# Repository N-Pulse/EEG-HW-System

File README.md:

# EEG Hardware System

This repository contains the hardware design files for the N-Pulse EEG system.

The project is divided into three main subsystems:

- `eeg-board/` — EEG acquisition electronics
- `power-board/` — power supply, battery management, charging, and protection
- `headset/` — mechanical headset design and electrode integration

The electronic boards are designed in KiCad. Git is used for version control and collaboration between team members.

## Repository structure

```text
eeg-hw-system/
├── eeg-board/
├── power-board/
├── headset/
└── README.md

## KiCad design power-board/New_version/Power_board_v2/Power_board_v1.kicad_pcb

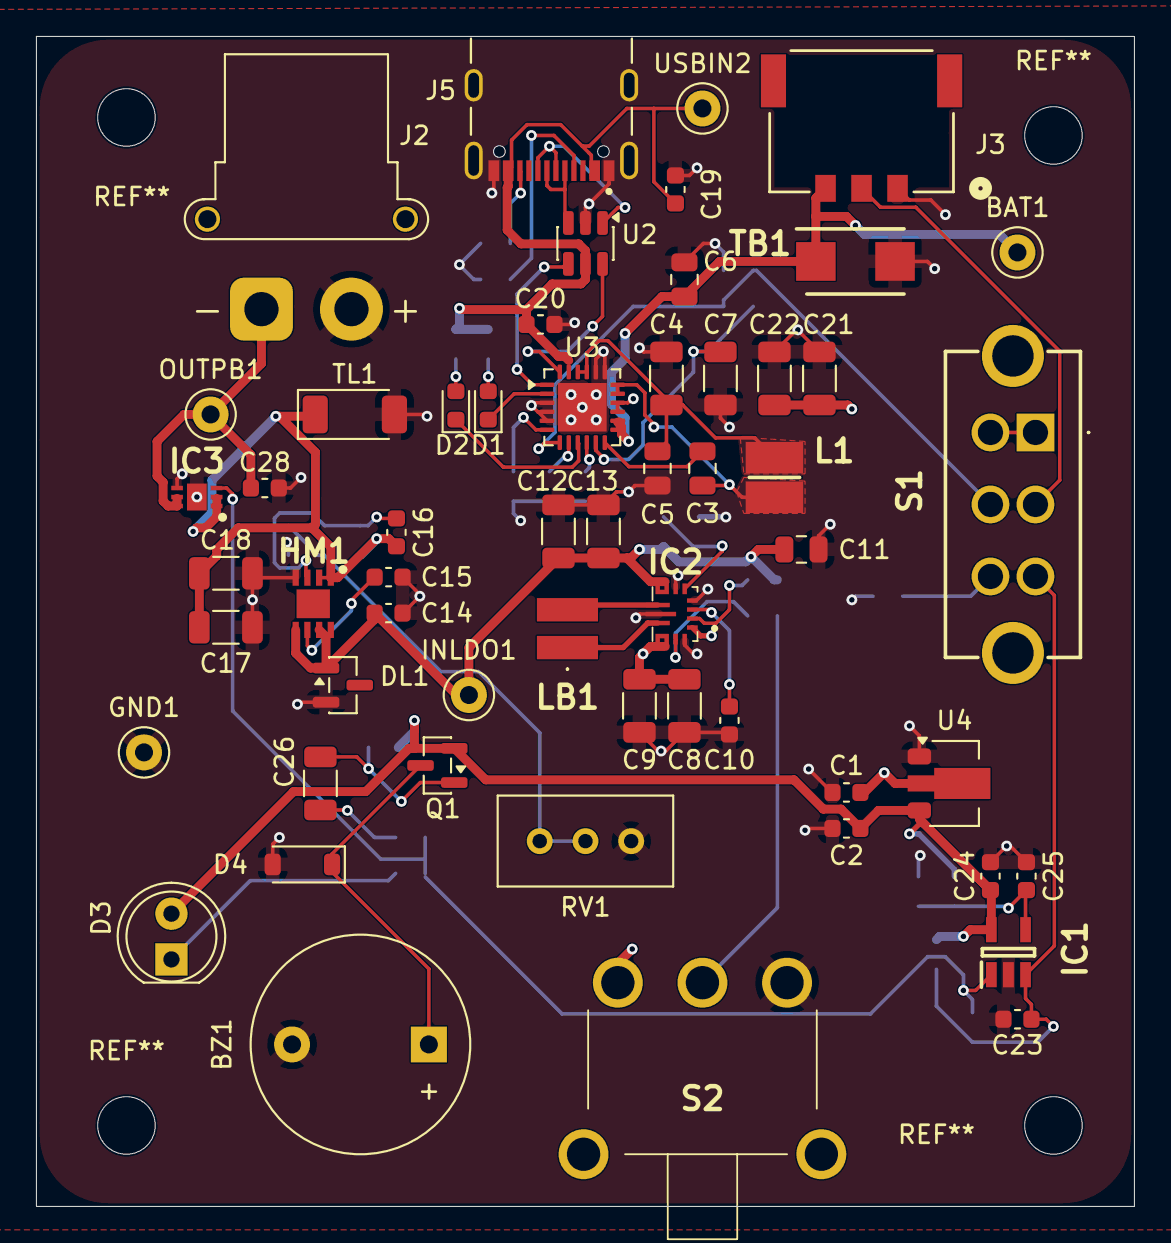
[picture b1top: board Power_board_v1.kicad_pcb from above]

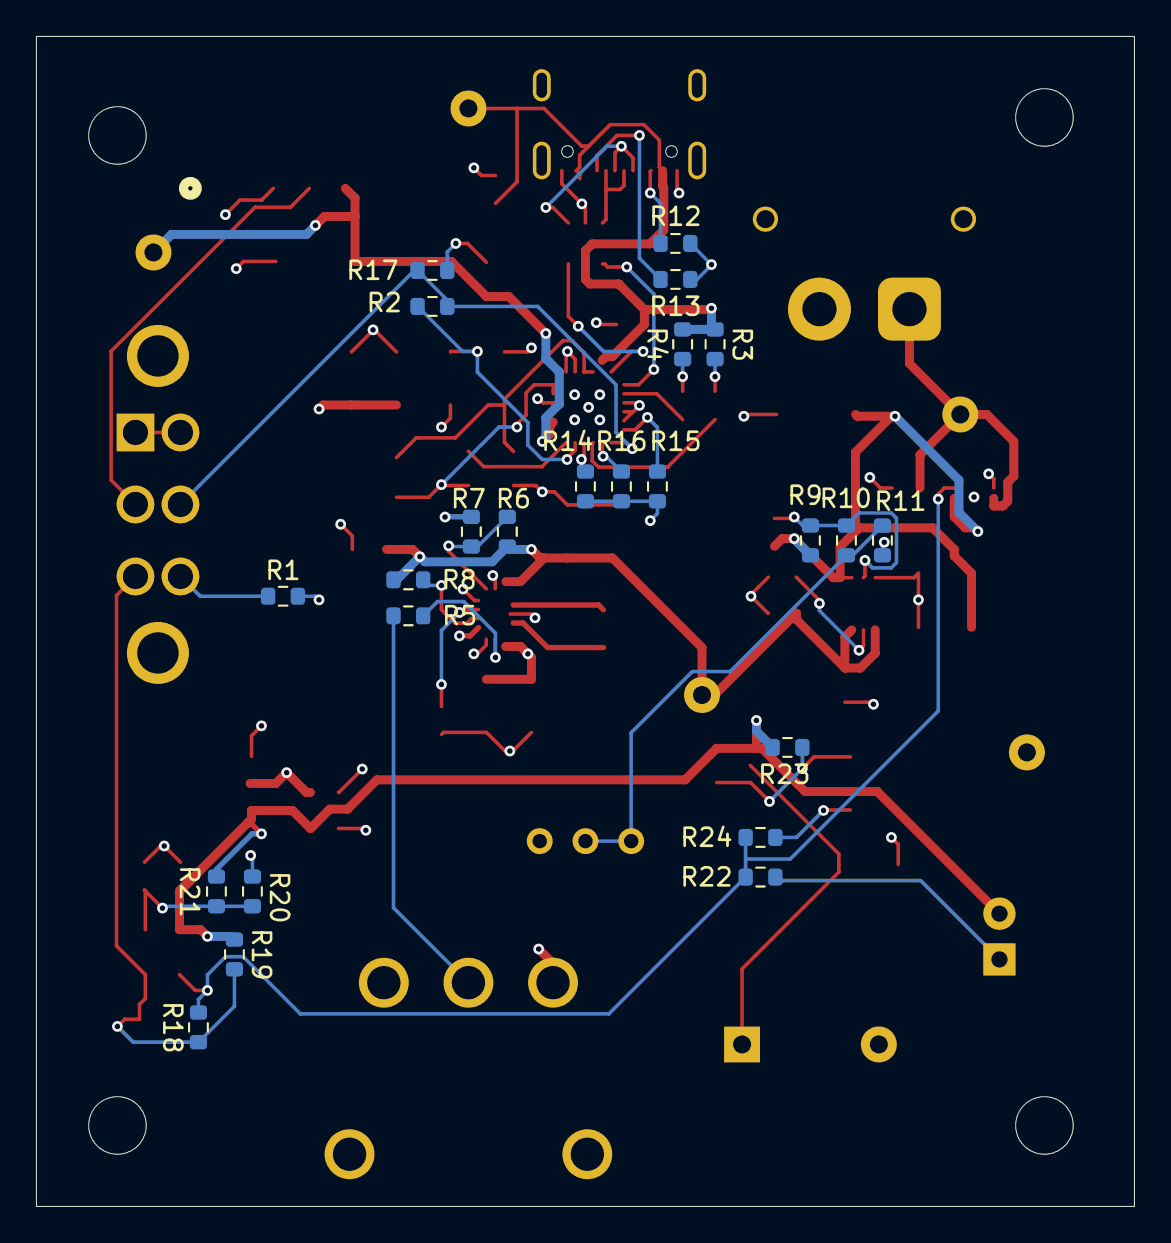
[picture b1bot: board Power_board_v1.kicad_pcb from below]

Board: 4 copper layers, 61.0 x 65.0 mm, 80 parts (24 on the bottom side), 46 nets.

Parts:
BAT1: TestPoint; TestPoint_Keystone_5000-5004_Miniature
BZ1: Buzzer; Buzzer_12x9.5RM7.6
C1, C2: 1uF; C_0603_1608Metric
C3: 47n; C_0805_2012Metric
C4, C21, C22: 22u; C_1206_3216Metric
C5, C6: 10u; C_0805_2012Metric
C7, C26: 4.7u; C_1206_3216Metric
C8, C9, C12, C13, C17, C18: 22uF; C_1206_3216Metric
C10, C14, C19, C23, C24, C25, C28: 100nF; C_0603_1608Metric
C11: 10uF; C_0805_2012Metric
C15: 220nF; C_0603_1608Metric
C16: 470nF; C_0603_1608Metric
C20: 1u; C_0603_1608Metric
D1, D2: LED_Small; LED_0603_1608Metric
D3: LED; LED_D5.0mm
D4: D; D_SOD-123
DL1: D_Zener; SOT-23
GND1: TestPoint; TestPoint_Keystone_5000-5004_Miniature
HM1: TPS7A8101DRBT; SON65P300X300X100-9N-D
IC1: MCP6541T-I_OT; SOT95P270X145-5N
IC2: TPS63070RNMR; TPS630701RNMR
IC3: AP2281-1FMG-7; SON50P201X181X60-7N
INLDO1: VinLDO; TestPoint_Keystone_5000-5004_Miniature
J2: XT30F; AMASS_XT30PW-F_1x02_P2.50mm_Horizontal
J3: 2053380003; CONN_2053380000-SD_03_MOL
J5: UJ20-C-H-G-SMT-1-P16-TR; SAMESKY_UJ20-C-H-G-SMT-1-P16-TR
L1: 1u; INDC3030X200N
LB1: 1.5uH; 78438336015
OUTPB1: VoutPB; TestPoint_Keystone_5000-5004_Miniature
Q1: BSS84; SOT-23
R1, R19, R20: 10k; R_0603_1608Metric
R2: 5.23k; R_0603_1608Metric
R3, R4, R24: 2.2k; R_0603_1608Metric
R5: 10kOhm; R_0603_1608Metric
R6: 665kOhm; R_0603_1608Metric
R7, R8: 100kOhm; R_0603_1608Metric
R9: 60.4k; R_0603_1608Metric
R10: 9.53k; R_0603_1608Metric
R11: 470; R_0603_1608Metric
R12, R13: 5.1k; R_0603_1608Metric
R14: 6.2k; R_0603_1608Metric
R15: 220k; R_0603_1608Metric
R16: 383; R_0603_1608Metric
R17: 30.1k; R_0603_1608Metric
R18: 51.1k; R_0603_1608Metric
R21: 26.7k; R_0603_1608Metric
R22: 330; R_0603_1608Metric
R23: 470k; R_0603_1608Metric
RV1: 0-500; Potentiometer_Bourns_3296W_Vertical
S1: MFS201N-9-Z; MFS201N9Z
S2: 5MS1S102AM6QES
TB1: D_Zener; DIOM5436X261N
TL1: D_SOD-128
U2: USBLC6-2SC6; SOT-23-6
U3: BQ25886RGE; Texas_RGE0024H_VQFN-24-1EP_4x4mm_P0.5mm_EP2.7x2.7mm
U4: MCP1703Ax-500xxMB; SOT-89-3
USBIN2: TestPoint; TestPoint_Keystone_5000-5004_Miniature

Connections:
/Buck 7.4 to 6.1V/EN: IC2.14 (EN), R5.2
/Buck 7.4 to 6.1V/FB: IC2.5 (FB), R6.2, R7.1
/Buck 7.4 to 6.1V/PG: IC2.2 (PG), R8.2
/Buck 7.4 to 6.1V/VAUX: C10.1, IC2.3 (VAUX)
/Buck 7.4 to 6.1V/VOUT BUCK BOOST: C11.1, C12.1, C13.1, C14.1, DL1.1 (K), HM1.5 (EN), HM1.7 (IN_1), HM1.8 (IN_2), IC2.7 (VOUT_1), IC2.8 (VOUT_2), IC2.17 (VOUT_1), INLDO1.1 (1_1), R6.1, R8.1
/Charging circuit/BTST: C3.2, U3.12 (BTST)
/Charging circuit/D+: U2.6 (I/O1), U3.24 (D+)
/Charging circuit/D-: U2.4 (I/O2), U3.1 (D-)
/Charging circuit/ICHGSET: R14.1, U3.10 (ICHGSET)
/Charging circuit/ILIM: R16.1, U3.8 (ILIM)
/Charging circuit/NTC: J3.2, S1.2 (COM_1)
/Charging circuit/PG: D2.1 (K), U3.9 (~PG)
/Charging circuit/PMID: C4.1, C5.1, L1.1, U3.21 (PMID), U3.22 (PMID)
/Charging circuit/REGN: C7.1, R2.1, U3.11 (REGN)
/Charging circuit/STAT: D1.1 (K), U3.2 (STAT)
/Charging circuit/SW: C3.1, L1.2, U3.17 (SW), U3.18 (SW)
/Charging circuit/SYS: C1.1, C8.1, C9.1, C21.1, C22.1, IC2.1 (PS/S), IC2.12 (VIN_1), IC2.13 (VIN_2), IC2.16 (VIN_1), S2.3 (NO), U3.15 (SYS), U3.16 (SYS), U4.2 (VI)
/Charging circuit/TS: R2.2, R17.1, S1.5 (COM_2), U3.7 (TS)
/Charging circuit/VBUS: C19.1, C20.1, J5.A4_B9 (VBUS), J5.B4_A9 (VBUS__1), R3.2, R4.2, U2.5 (VBUS), U3.23 (VBUS), USBIN2.1 (1_1)
/Charging circuit/VSET: R15.1, U3.6 (VSET)
/Temperature control/5V: C2.1, C24.1, D3.2 (A), IC1.5 (VDD), Q1.2 (S), R19.1, R21.1, R23.1, U4.3 (VO)
/Temperature control/INCOMP: C23.1, IC1.3 (VIN+), R18.1, R19.2, S1.3 (NC_1)
/Temperature control/OUT: IC1.1 (OUT), IC3.3 (EN), R18.2, R22.2, R24.2
BATTERY VOLTAGE: BAT1.1 (1_1), C6.1, J3.3, TB1.1 (K), U3.13 (BAT), U3.14 (BAT)
GND: BZ1.2 (-), C1.2, C2.2, C4.2, C5.2, C6.2, C7.2, C8.2, C9.2, C10.2, C11.2, C12.2, C13.2, C14.2, C15.2, C17.2, C18.2, C19.2, C20.2, C21.2, C22.2, C23.2, C24.2, C25.2, C28.2, D4.2 (A), DL1.2 (A), GND1.1 (1_1), HM1.4 (GND), IC1.2 (VSS), IC2.4 (GND), IC2.6 (FB2), IC2.10 (PGND), IC2.15 (VSEL), IC3.4 (GND_1), IC3.7 (GND_2), J2.2, J3.1, J5.A1_B12 (GND), J5.B1_A12 (GND__1), J5.SH1 (SHIELD), J5.SH2 (SHIELD__1), J5.SH3 (SHIELD__2), J5.SH4 (SHIELD__3), R1.2, R7.2, R11.2, R12.2, R13.2, R14.2, R15.2, R16.2, R17.2, R20.2, RV1.3, S2.1 (NC), TB1.2 (A), TL1.2 (A), U2.2 (GND), U3.3 (~CE), U3.4 (GND), U3.5 (OTG), U3.19 (GND), U3.20 (GND), U3.25 (GND), U4.1 (GND)
unnamed: BZ1.1 (+), D4.1 (K), Q1.3 (D)
unnamed: C26.2, R24.1
unnamed: D1.2 (A), R4.1
unnamed: D2.2 (A), R3.1
unnamed: D3.1 (K), R22.1
unnamed: C16.2, HM1.3 (FB/SNS), R9.2, R10.1
unnamed: C15.1, HM1.6 (NR)
unnamed: C16.1, C17.1, C18.1, HM1.1 (OUT_1), HM1.2 (OUT_2), IC3.1 (IN_1), IC3.2 (IN_2), R9.1, TL1.1 (K)
unnamed: C25.1, IC1.4 (VIN-), R20.1, R21.2
unnamed: IC2.11 (L1), LB1.1
unnamed: IC2.9 (L2), LB1.2
unnamed: J5.A5 (CC1), R13.1
unnamed: J5.B5 (CC2), R12.1
unnamed: J5.A7 (DN1), J5.B7 (DN2), U2.3 (I/O2)
unnamed: J5.A6 (DP1), J5.B6 (DP2), U2.1 (I/O1)
unnamed: C26.1, Q1.1 (G), R23.2
unnamed: R10.2, R11.1, RV1.1, RV1.2
unnamed: R1.1, S1.6 (NC_2)
unnamed: S1.1 (NO_1), S1.4 (NO_2)
unnamed: R5.1, S2.2 (COM)
VOUT PB: C28.1, IC3.5 (OUT_1), IC3.6 (OUT_2), J2.1, OUTPB1.1 (1_1)

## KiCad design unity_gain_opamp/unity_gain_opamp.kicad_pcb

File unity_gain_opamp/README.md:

# N-Pulse Workshop Board

A teaching board for the N-Pulse electronics workshop: an ESP32-S3 platform with
a complete battery power path, four sensors, and a heart-rate (PPG) front end —
designed so that new members can learn hardware design by reading a real,
working board rather than a toy example.

## What this board is for

Most beginner projects are one circuit. This board is deliberately the opposite:
it puts one worked example of nearly every subsystem you meet in real hardware
onto a single PCB, so that "how do I charge a battery?", "how do I protect a USB
port?" or "how do I amplify a microvolt sensor?" all have an answer you can hold
in your hand and probe with a scope.

It is a **reference**, not a first project. Read it, measure it, copy from it.

Every design decision is documented in **[DESIGN_NOTES.md](DESIGN_NOTES.md)**,
which also contains general guidance on how to draw a good schematic and how to
lay out a good PCB.

## Features

**Power**
- USB-C input with ESD protection and a TVS on VBUS
- MCP73833 Li-ion charger (1 A) with charge / done / power-good indicators
- BQ29728 cell protection with back-to-back MOSFETs
- TPS631000 buck-boost — holds 3.3 V across the whole 4.2 → 3.0 V cell range
- TPS2116 priority mux — runs from USB when present, battery otherwise
- TPS2068 load switch — firmware can cut power to the peripherals
- Two rails: `+3V3_ESP32` (always on) and `+3V3` (switched)

**Sensing**
- SHT40 — humidity and temperature (I²C)
- LIS2DW12 — 3-axis accelerometer with interrupts, on the always-on rail so the
  board can wake on motion
- MCP9700A — analog temperature
- PPG pulse sensor — LED + photodiode into a two-stage bandpass amplifier
  (0.34–5 Hz, gain ×121)

**Interfaces**
- ESP32-S3-WROOM-1, programmed over native USB — no bridge chip, no drivers
- microSD card slot with mechanical card detect
- Two RGB LEDs and a piezo buzzer
- I²C expansion header
- 17 labelled test points

**Physical:** 70 × 80 mm, 2-layer, 142 components, four M4 mounting holes.

## Using the board

**Powering it.** Plug in USB-C and it runs, regardless of the ON/OFF switch. On
battery, slide the ON/OFF switch (bottom edge, marked `ON`/`OFF`). With USB
connected the board runs from USB and charges the cell at the same time.

**Charging.** The three LEDs on the left edge are, top to bottom, `CHRG`
(charging), `DONE` (complete) and `PG` (USB power good).

**Programming.** Connect USB-C — the board enumerates directly as an ESP32-S3.
Normally you can just flash it. If you need to force download mode: slide the
`BOOT0` switch (right edge) to the boot position, press `ENABLE` to reset, flash,
then slide it back and reset again. The LED beside the switch shows its position.

**Reading your pulse.** Rest a fingertip on the fingerprint symbol in the middle
of the board, covering the LED and photodiode, with light steady pressure. The
amplifier needs a second or two to settle. Signal quality depends a lot on
contact pressure and ambient light — that is part of what makes it a good
teaching circuit.

**I²C expansion.** The 4-pin header on the right edge is `3V3 / SDA / SCL / GND`
(labelled on the silkscreen). It is ESD-protected and shares the bus with the
on-board sensors, so remember the address space is shared.

**Test points.** Every rail and every interesting node is brought out:
`+5V USB`, `3V3 USB`, `3V3 BATT`, `3V3 ESP32`, `3V3`, `+BATT`, `-BATT`, `GND`,
plus `FB`, `PR1`, `MODE` and `PWR SW` for the power circuits.

## Opening the project

Built with **KiCad 9/10**. Clone and open `Electronics_Workwhop_PCB.kicad_pro`.

All custom symbols and footprints live in the repository — `N_pulse.pretty/` for
footprints and `Library/` for vendor symbol libraries — so the project should
open with no missing parts. Nothing needs to be installed globally.

```
Electronics_Workwhop_PCB.kicad_pro   project file — open this
├── Architecture.kicad_sch           top-level sheet
├── ESP32.kicad_sch                  MCU, SD card, LEDs, buzzer, buttons
├── Power_management.kicad_sch       USB-C, charger, protection, regulators
├── Sensors.kicad_sch                SHT40, accelerometer, temperature, PPG
└── Electronics_Workwhop_PCB.kicad_pcb
DESIGN_NOTES.md                      why the circuits look the way they do
docs/                                images and documentation assets
```

## Pin map

See [Appendix A of DESIGN_NOTES.md](DESIGN_NOTES.md) for the full table,
generated from the netlist.

The one rule worth memorising: **analog inputs must be on ADC1 (IO1–IO10)**.
ADC2 cannot be read while Wi-Fi is running.

## Contributing

KiCad files cannot be merged. If two people edit the same sheet at the same
time, git produces a conflict that no one can resolve by hand.

Before you start work, say which sheet you are taking, and pull before you open
the project. Commit with a message describing the change, not just "update".

The pre-fabrication checklist in
[Appendix B of DESIGN_NOTES.md](DESIGN_NOTES.md) should be run before any board
is ordered.

---

> *"What I cannot create, I do not understand."* — Richard Feynman
>
> (also printed on the board)

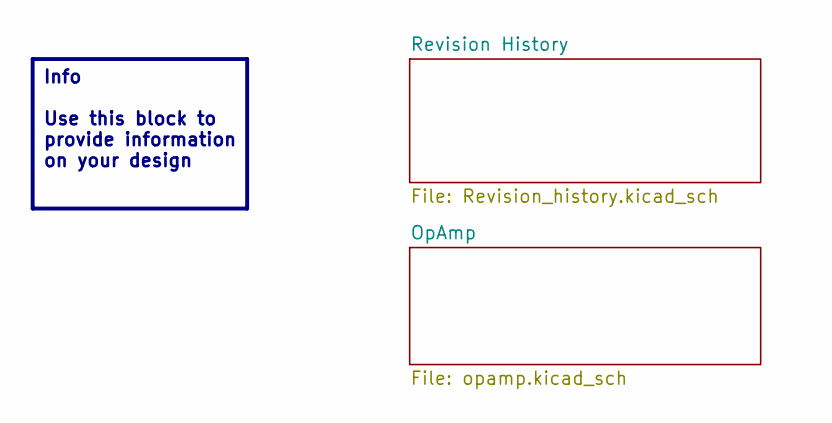
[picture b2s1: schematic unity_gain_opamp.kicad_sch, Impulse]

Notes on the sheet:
Info Use this block to provide information on your design

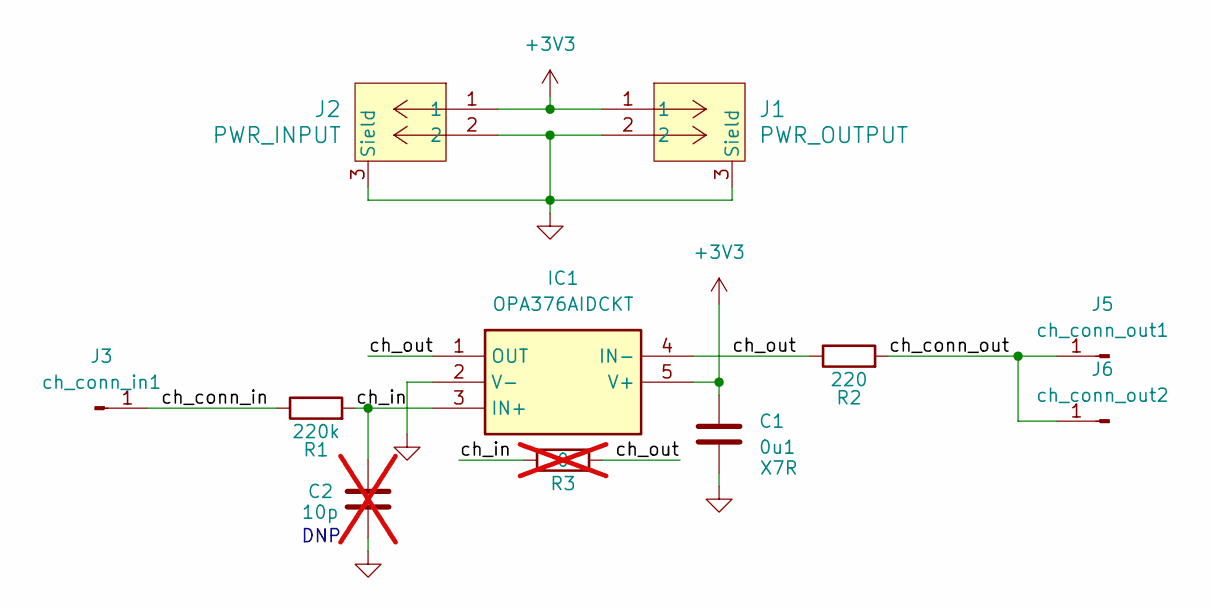
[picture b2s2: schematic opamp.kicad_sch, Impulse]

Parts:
C1: 0u1; C_0805_2012Metric
C2: 10p; C_0805_2012Metric; not fitted
IC1: OPA376AIDCKT; SOT-353_SC-70-5; Manufacturer_Part_Number OPA376AIDCKT
J1: PWR_OUTPUT; CONN_5037630000-SD_02_MOL
J2: PWR_INPUT; CONN_5037630000-SD_02_MOL
J3: ch_conn_in1; electrode
J5: ch_conn_out1; SolderWire-0.75sqmm_1x01_D1.25mm_OD2.3mm_Relief
J6: ch_conn_out2; PinHeader_1x01_P2.54mm_Horizontal
R1: 220k; R_0805_2012Metric
R2: 220; R_0805_2012Metric
R3: 0; R_0805_2012Metric; not fitted

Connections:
+3V3: C1.1, IC1.5 (V+), J1.1, J2.1
/OpAmp/ch_conn_in: J3.1 (Pin_1_1), R1.1
/OpAmp/ch_conn_out: J5.1 (Pin_1_1), J6.1 (Pin_1_1), R2.2
/OpAmp/ch_in: C2.1, IC1.3 (IN+), R1.2, R3.1
/OpAmp/ch_out: IC1.1 (OUT), IC1.4 (IN-), R2.1, R3.2
GND: C1.2, C2.2, IC1.2 (V-), J1.2, J1.3 (Sield), J1.4 (Sield), J2.2, J2.3 (Sield), J2.4 (Sield)

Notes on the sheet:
DNP

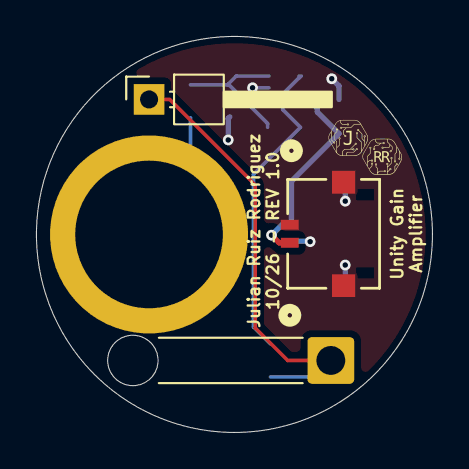
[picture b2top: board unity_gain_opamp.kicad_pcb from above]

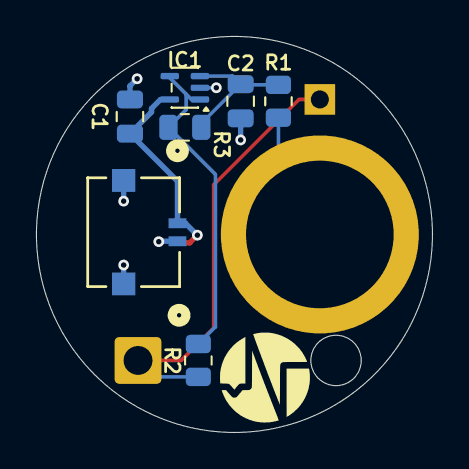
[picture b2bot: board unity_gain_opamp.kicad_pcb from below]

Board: 2 copper layers, 22.0 x 22.0 mm, 11 parts (7 on the bottom side), 6 nets.
